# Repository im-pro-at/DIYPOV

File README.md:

# DIYPOV
 One POV Display to rule them all!

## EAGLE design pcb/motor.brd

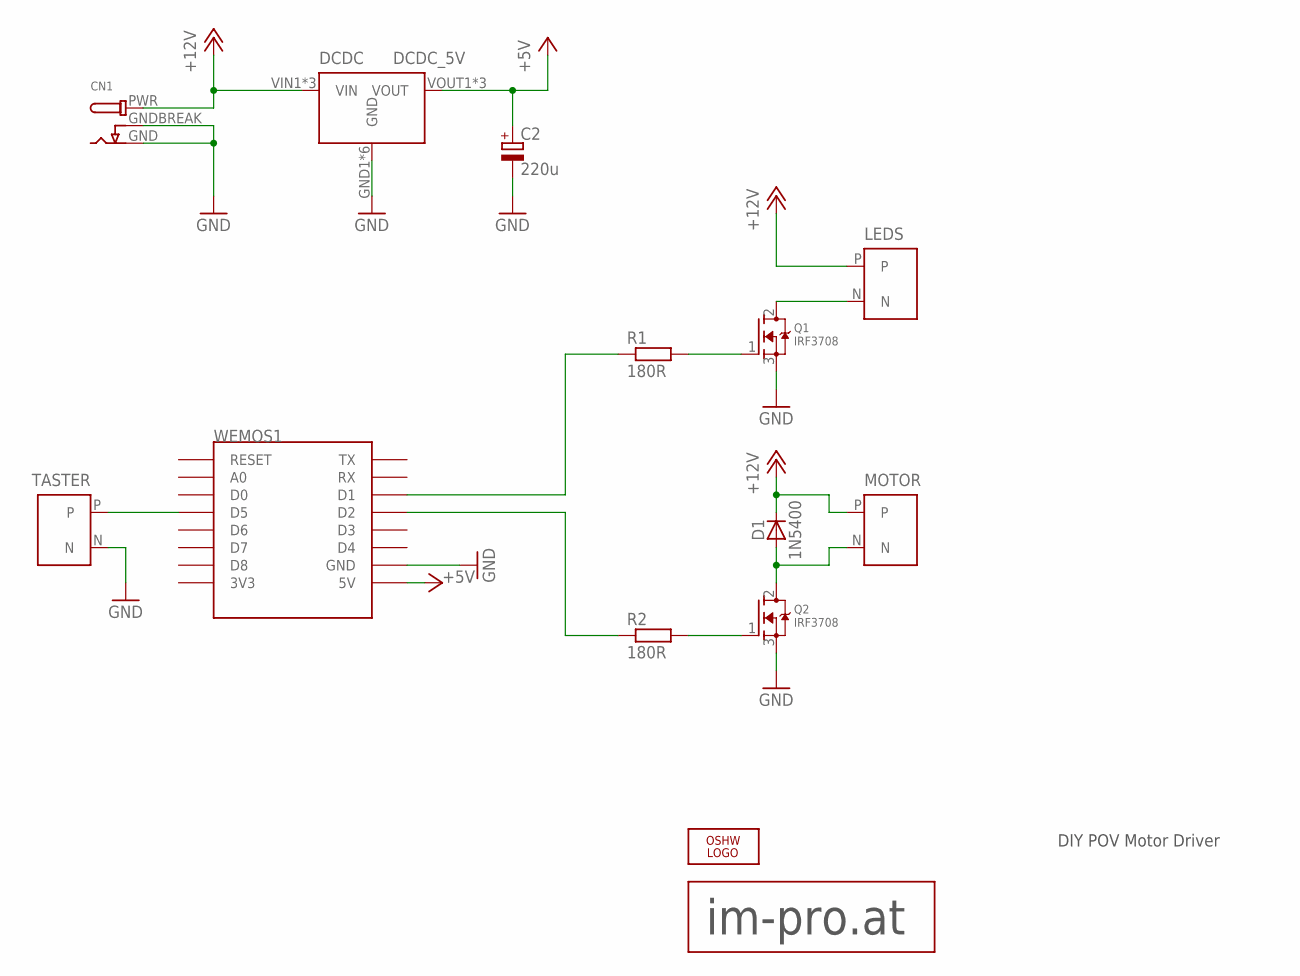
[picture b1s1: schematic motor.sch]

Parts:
C2: 220u; E3,5-8
CN1: DCBARRELPTH; DCJACK_2MM_PTH
D1: 1N5400; DO201-15
DCDC: DCDC_5V; DCDC
LEDS: TX30; XT30
LOGO1: OSHW_LOGO_FILLX0350-NT; OSHW_FILLX350_NOTEXT
MOTOR: TX30; XT30
Q1, Q2: IRF3708; TO220V
R1, R2: 180R; 0207/10
TASTER: TX30; XT30
U$1: LOGO20MM; LOGO_20MM
WEMOS1: WEMOS-D1-MINI

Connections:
+5V: C2.+, DCDC.VOUT1 (VOUT), DCDC.VOUT2 (VOUT), DCDC.VOUT3 (VOUT), WEMOS1.5V
+12V: CN1.PWR, D1.C, DCDC.VIN1 (VIN), DCDC.VIN2 (VIN), DCDC.VIN3 (VIN), LEDS.P, MOTOR.P
GND: C2.-, CN1.GND, CN1.GNDBREAK, DCDC.GND1 (GND), DCDC.GND2 (GND), DCDC.GND3 (GND), DCDC.GND4 (GND), DCDC.GND5 (GND), DCDC.GND6 (GND), Q1.3 (S), Q2.3 (S), TASTER.N, WEMOS1.GND
unnamed: D1.A, MOTOR.N, Q2.2 (D)
unnamed: LEDS.N, Q1.2 (D)
unnamed: R1.1, WEMOS1.D1
unnamed: TASTER.P, WEMOS1.D5
unnamed: R2.1, WEMOS1.D2
unnamed: Q2.1 (G), R2.2
unnamed: Q1.1 (G), R1.2

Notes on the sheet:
DIY POV Motor Driver

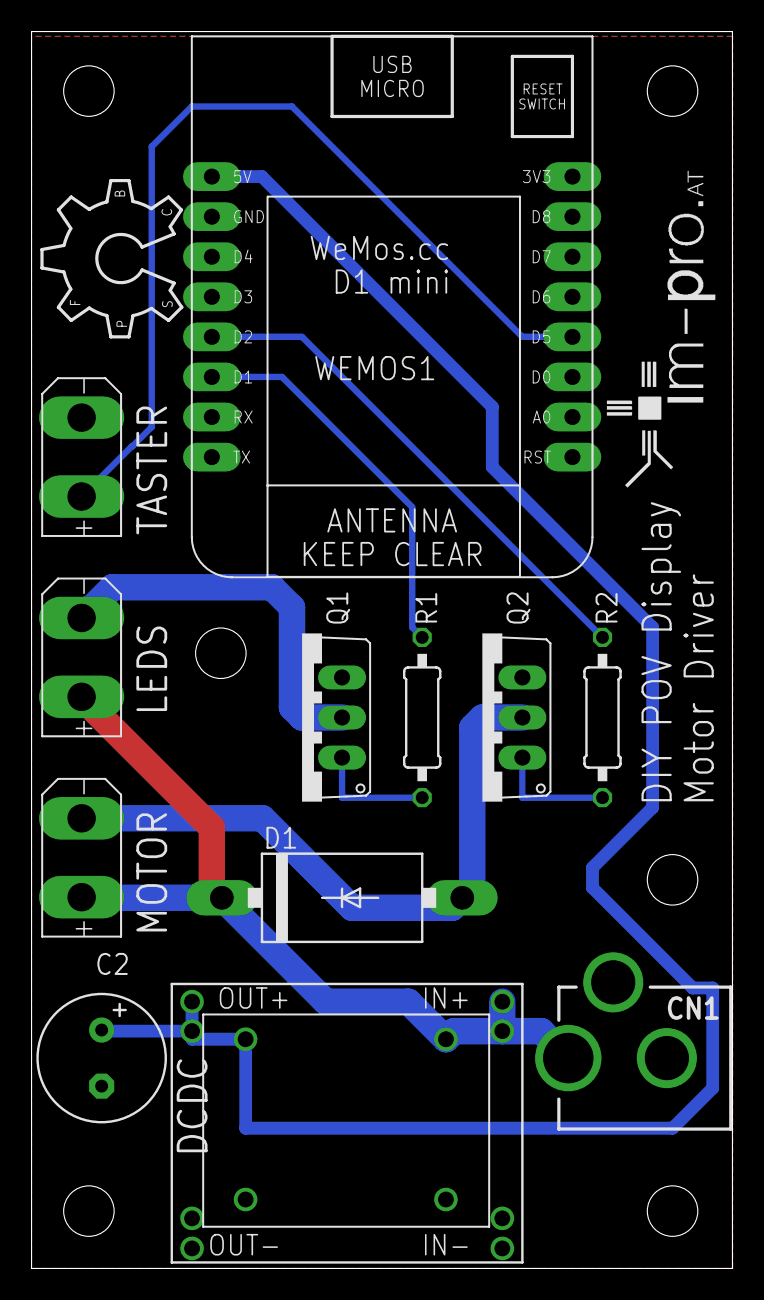
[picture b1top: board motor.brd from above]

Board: 2 copper layers, 44.4 x 78.4 mm, 14 parts (0 on the bottom side), 10 nets.

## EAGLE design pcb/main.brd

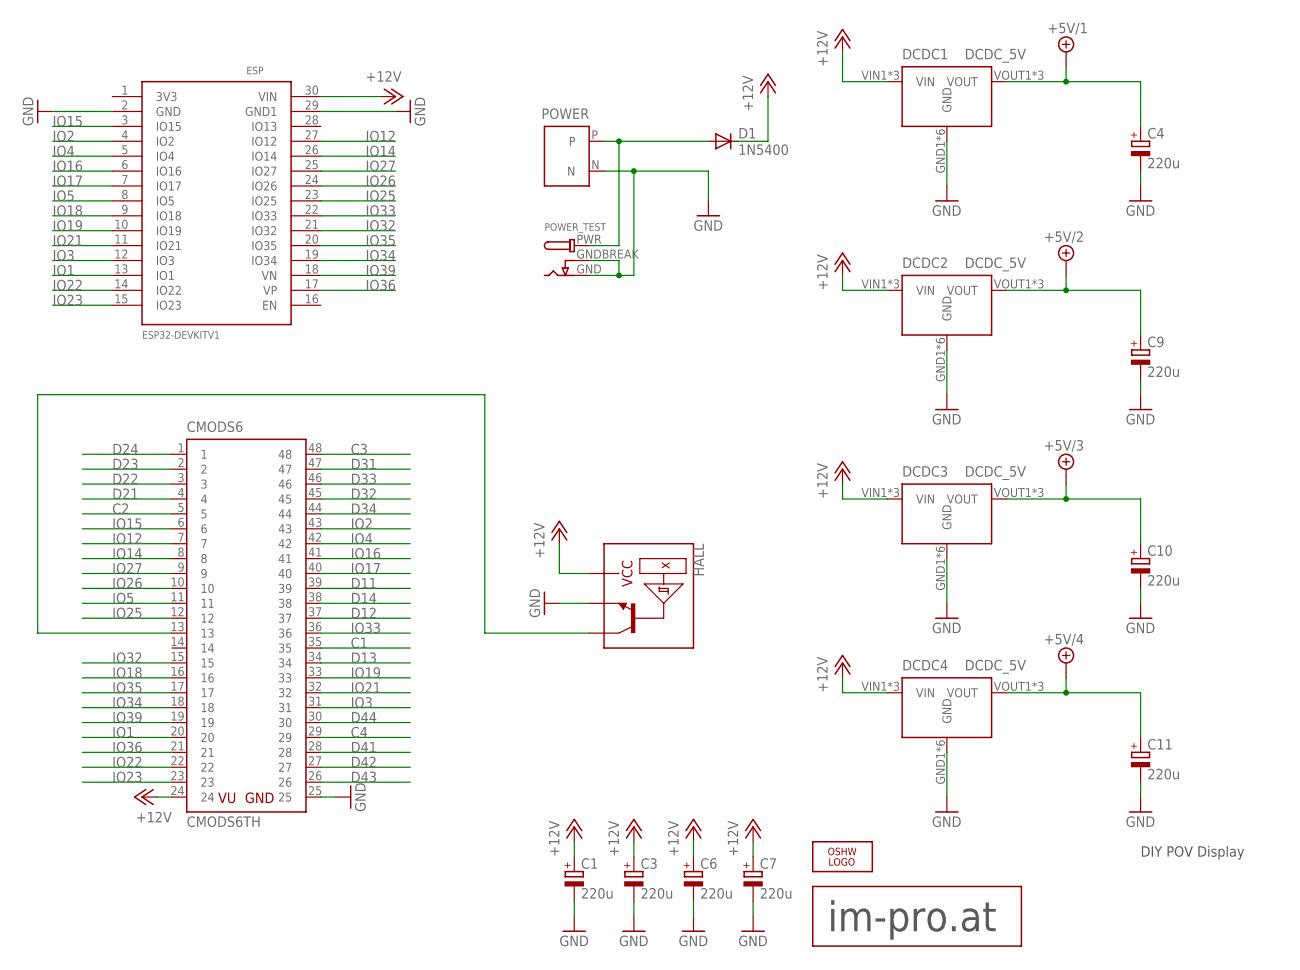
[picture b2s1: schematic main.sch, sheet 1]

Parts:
C1, C3, C4, C6, C7, C9, C10, C11: 220u; E3,5-8
CMODS6: CMODS6TH; DIL48
D1: 1N5400; DO201-15
DCDC1, DCDC2, DCDC3, DCDC4: DCDC_5V; DCDC
ESP: ESP32DEVKITV1; ESP32-DEVKITV1
HALL: HALL
LOGO1: OSHW_LOGO_FILLX0350-NT; OSHW_FILLX350_NOTEXT
POWER: TX30; XT30
POWER_TEST: DCBARRELPTH; DCJACK_2MM_PTH
U$2: LOGO20MM; LOGO_20MM

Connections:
+5V/1: C4.+, DCDC1.VOUT1 (VOUT), DCDC1.VOUT2 (VOUT), DCDC1.VOUT3 (VOUT); also elsewhere on the board
+5V/2: C9.+, DCDC2.VOUT1 (VOUT), DCDC2.VOUT2 (VOUT), DCDC2.VOUT3 (VOUT); also elsewhere on the board
+5V/3: C10.+, DCDC3.VOUT1 (VOUT), DCDC3.VOUT2 (VOUT), DCDC3.VOUT3 (VOUT); also elsewhere on the board
+5V/4: C11.+, DCDC4.VOUT1 (VOUT), DCDC4.VOUT2 (VOUT), DCDC4.VOUT3 (VOUT); also elsewhere on the board
+12V: C1.+, C3.+, C6.+, C7.+, CMODS6.24, D1.C, DCDC1.VIN1 (VIN), DCDC1.VIN2 (VIN), DCDC1.VIN3 (VIN), DCDC2.VIN1 (VIN), DCDC2.VIN2 (VIN), DCDC2.VIN3 (VIN), DCDC3.VIN1 (VIN), DCDC3.VIN2 (VIN), DCDC3.VIN3 (VIN), DCDC4.VIN1 (VIN), DCDC4.VIN2 (VIN), DCDC4.VIN3 (VIN), ESP.30 (VIN), HALL.VCC
C1: CMODS6.35; also elsewhere on the board
C2: CMODS6.5; also elsewhere on the board
C3: CMODS6.48; also elsewhere on the board
C4: CMODS6.29; also elsewhere on the board
D11: CMODS6.39; also elsewhere on the board
D12: CMODS6.37; also elsewhere on the board
D13: CMODS6.34; also elsewhere on the board
D14: CMODS6.38; also elsewhere on the board
D21: CMODS6.4; also elsewhere on the board
D22: CMODS6.3; also elsewhere on the board
D23: CMODS6.2; also elsewhere on the board
D24: CMODS6.1; also elsewhere on the board
D31: CMODS6.47; also elsewhere on the board
D32: CMODS6.45; also elsewhere on the board
D33: CMODS6.46; also elsewhere on the board
D34: CMODS6.44; also elsewhere on the board
D41: CMODS6.28; also elsewhere on the board
D42: CMODS6.27; also elsewhere on the board
D43: CMODS6.26; also elsewhere on the board
D44: CMODS6.30; also elsewhere on the board
GND: C1.-, C3.-, C4.-, C6.-, C7.-, C9.-, C10.-, C11.-, CMODS6.25, DCDC1.GND1 (GND), DCDC1.GND2 (GND), DCDC1.GND3 (GND), DCDC1.GND4 (GND), DCDC1.GND5 (GND), DCDC1.GND6 (GND), DCDC2.GND1 (GND), DCDC2.GND2 (GND), DCDC2.GND3 (GND), DCDC2.GND4 (GND), DCDC2.GND5 (GND), DCDC2.GND6 (GND), DCDC3.GND1 (GND), DCDC3.GND2 (GND), DCDC3.GND3 (GND), DCDC3.GND4 (GND), DCDC3.GND5 (GND), DCDC3.GND6 (GND), DCDC4.GND1 (GND), DCDC4.GND2 (GND), DCDC4.GND3 (GND), DCDC4.GND4 (GND), DCDC4.GND5 (GND), DCDC4.GND6 (GND), ESP.2 (GND), ESP.29 (GND1), HALL.GND, POWER.N, POWER_TEST.GND, POWER_TEST.GNDBREAK; also elsewhere on the board
IO1: CMODS6.20, ESP.13 (IO1)
IO2: CMODS6.43, ESP.4 (IO2)
IO3: CMODS6.31, ESP.12 (IO3)
IO4: CMODS6.42, ESP.5 (IO4)
IO5: CMODS6.11, ESP.8 (IO5)
IO12: CMODS6.7, ESP.27 (IO12)
IO14: CMODS6.8, ESP.26 (IO14)
IO15: CMODS6.6, ESP.3 (IO15)
IO16: CMODS6.41, ESP.6 (IO16)
IO17: CMODS6.40, ESP.7 (IO17)
IO18: CMODS6.16, ESP.9 (IO18)
IO19: CMODS6.33, ESP.10 (IO19)
IO21: CMODS6.32, ESP.11 (IO21)
IO22: CMODS6.22, ESP.14 (IO22)
IO23: CMODS6.23, ESP.15 (IO23)
IO25: CMODS6.12, ESP.23 (IO25)
IO26: CMODS6.10, ESP.24 (IO26)
IO27: CMODS6.9, ESP.25 (IO27)
IO32: CMODS6.15, ESP.21 (IO32)
IO33: CMODS6.36, ESP.22 (IO33)
IO34: CMODS6.18, ESP.19 (IO34)
IO35: CMODS6.17, ESP.20 (IO35)
IO36: CMODS6.21, ESP.17 (VP)
IO39: CMODS6.19, ESP.18 (VN)
unnamed: CMODS6.13, HALL.OUT
unnamed: D1.A, POWER.P, POWER_TEST.PWR

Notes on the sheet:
DIY POV Display

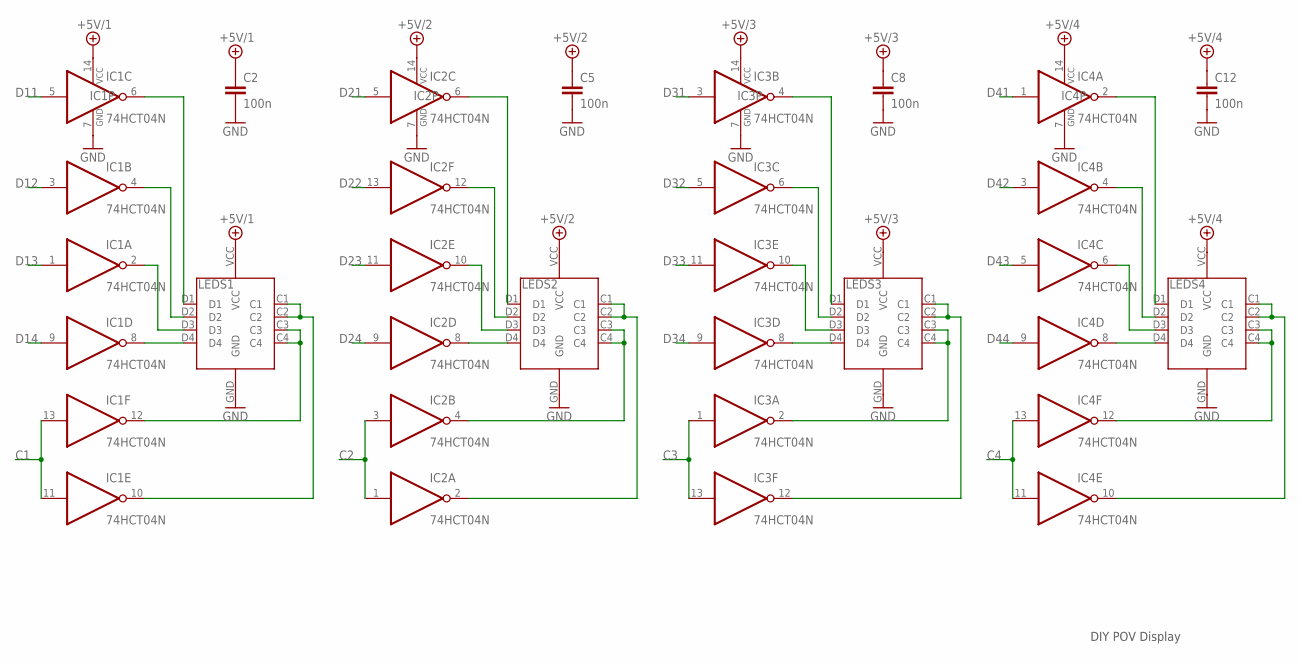
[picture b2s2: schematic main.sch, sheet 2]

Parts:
C2, C5, C8, C12: 100n; C025_050-025X075
IC1, IC2, IC3, IC4: 74HCT04N; DIL14
LEDS1, LEDS2, LEDS3, LEDS4: LEDCON

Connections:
+5V/1: C2.1, IC1.14 (VCC), LEDS1.VCC; also elsewhere on the board
+5V/2: C5.1, IC2.14 (VCC), LEDS2.VCC; also elsewhere on the board
+5V/3: C8.1, IC3.14 (VCC), LEDS3.VCC; also elsewhere on the board
+5V/4: C12.1, IC4.14 (VCC), LEDS4.VCC; also elsewhere on the board
C1: IC1.11 (I), IC1.13 (I); also elsewhere on the board
C2: IC2.1 (I), IC2.3 (I); also elsewhere on the board
C3: IC3.1 (I), IC3.13 (I); also elsewhere on the board
C4: IC4.11 (I), IC4.13 (I); also elsewhere on the board
D11: IC1.5 (I); also elsewhere on the board
D12: IC1.3 (I); also elsewhere on the board
D13: IC1.1 (I); also elsewhere on the board
D14: IC1.9 (I); also elsewhere on the board
D21: IC2.5 (I); also elsewhere on the board
D22: IC2.13 (I); also elsewhere on the board
D23: IC2.11 (I); also elsewhere on the board
D24: IC2.9 (I); also elsewhere on the board
D31: IC3.3 (I); also elsewhere on the board
D32: IC3.5 (I); also elsewhere on the board
D33: IC3.11 (I); also elsewhere on the board
D34: IC3.9 (I); also elsewhere on the board
D41: IC4.1 (I); also elsewhere on the board
D42: IC4.3 (I); also elsewhere on the board
D43: IC4.5 (I); also elsewhere on the board
D44: IC4.9 (I); also elsewhere on the board
GND: C2.2, C2.3 (2), C5.2, C5.3 (2), C8.2, C8.3 (2), C12.2, C12.3 (2), IC1.7 (GND), IC2.7 (GND), IC3.7 (GND), IC4.7 (GND), LEDS1.GND, LEDS2.GND, LEDS3.GND, LEDS4.GND; also elsewhere on the board
unnamed: IC1.8 (O), LEDS1.D4
unnamed: IC1.2 (O), LEDS1.D3
unnamed: IC1.4 (O), LEDS1.D2
unnamed: IC1.6 (O), LEDS1.D1
unnamed: IC1.12 (O), LEDS1.C3, LEDS1.C4
unnamed: IC1.10 (O), LEDS1.C1, LEDS1.C2
unnamed: IC2.8 (O), LEDS2.D4
unnamed: IC2.10 (O), LEDS2.D3
unnamed: IC2.12 (O), LEDS2.D2
unnamed: IC2.6 (O), LEDS2.D1
unnamed: IC2.4 (O), LEDS2.C3, LEDS2.C4
unnamed: IC2.2 (O), LEDS2.C1, LEDS2.C2
unnamed: IC3.8 (O), LEDS3.D4
unnamed: IC3.10 (O), LEDS3.D3
unnamed: IC3.6 (O), LEDS3.D2
unnamed: IC3.4 (O), LEDS3.D1
unnamed: IC3.2 (O), LEDS3.C3, LEDS3.C4
unnamed: IC3.12 (O), LEDS3.C1, LEDS3.C2
unnamed: IC4.8 (O), LEDS4.D4
unnamed: IC4.6 (O), LEDS4.D3
unnamed: IC4.4 (O), LEDS4.D2
unnamed: IC4.2 (O), LEDS4.D1
unnamed: IC4.12 (O), LEDS4.C3, LEDS4.C4
unnamed: IC4.10 (O), LEDS4.C1, LEDS4.C2

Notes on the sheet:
DIY POV Display

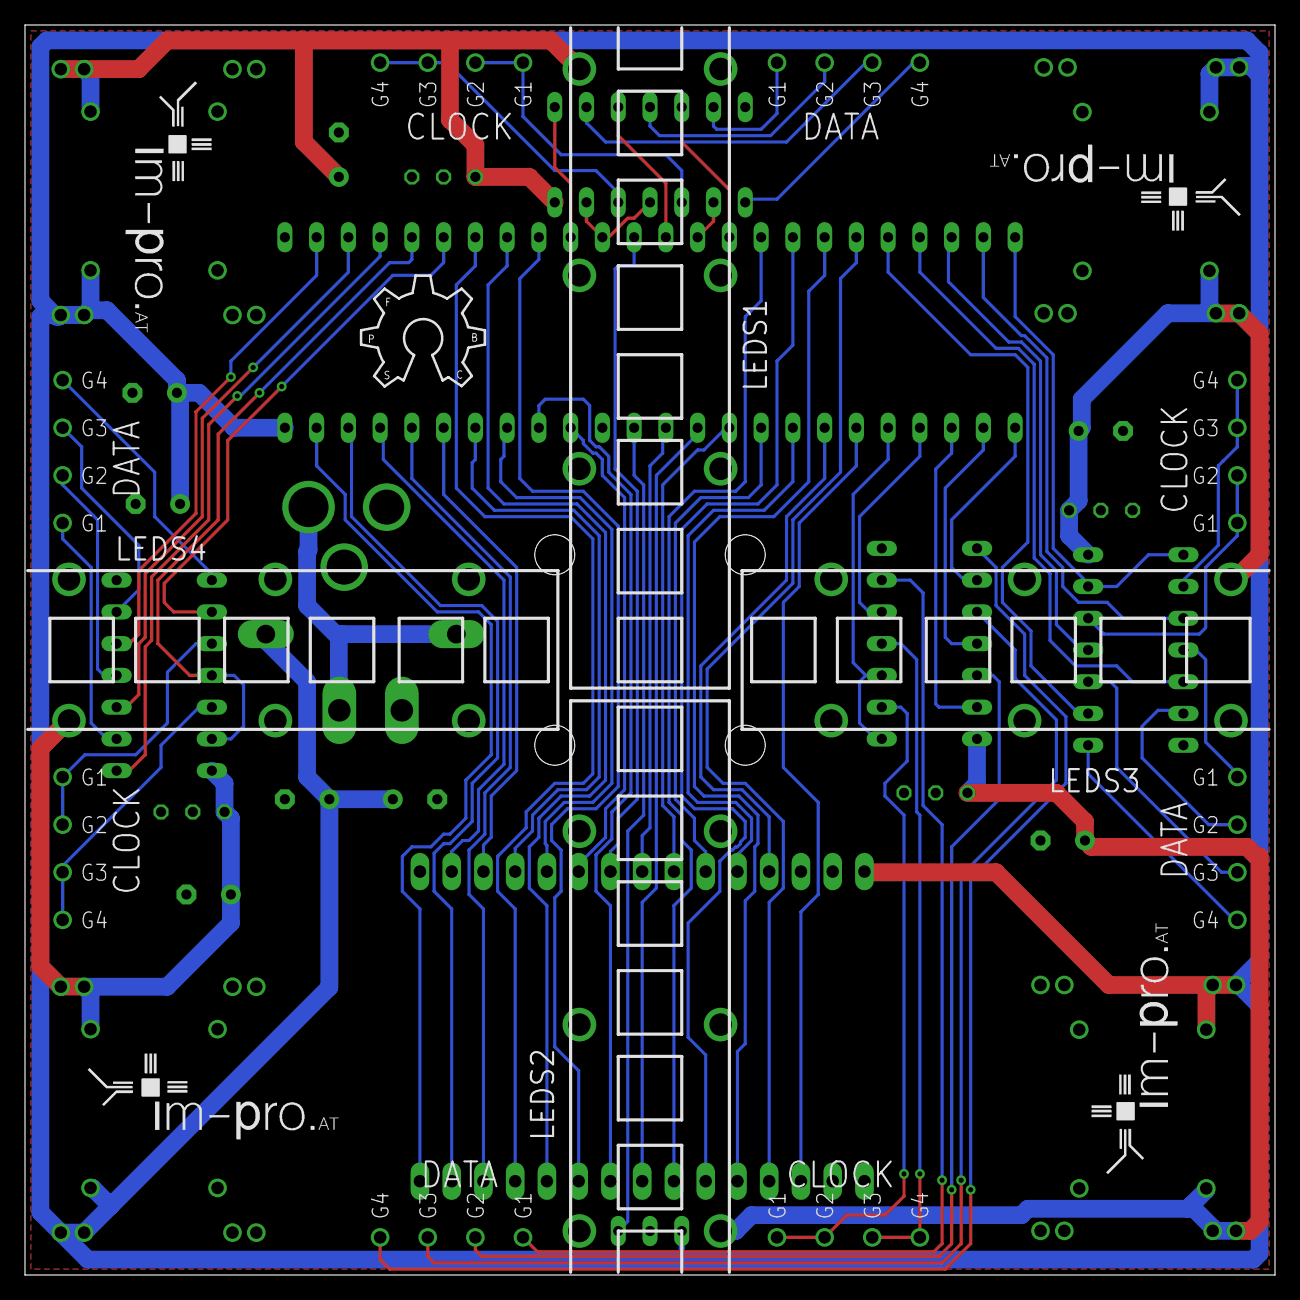
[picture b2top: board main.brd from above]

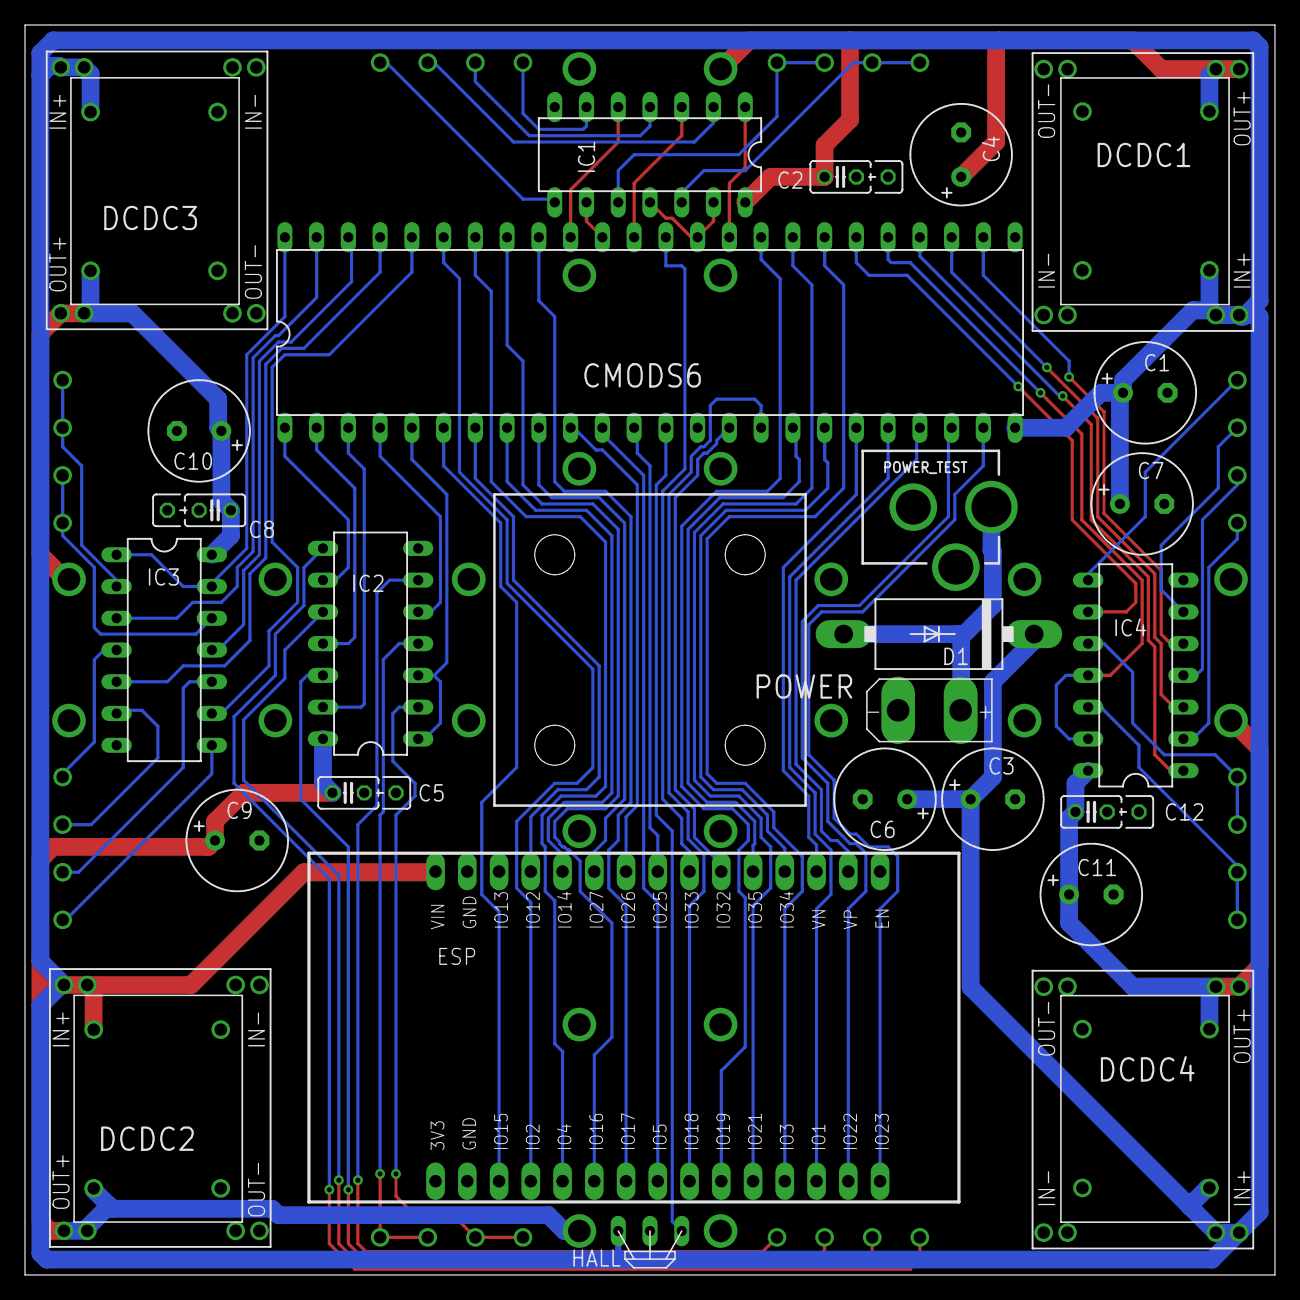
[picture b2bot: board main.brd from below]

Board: 2 copper layers, 100.0 x 100.0 mm, 35 parts (26 on the bottom side), 76 nets.

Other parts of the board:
U$1, U$3, U$4: LOGO20MM; LOGO_20MM

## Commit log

2019-08-28 Initial commit: Copied data from POV project
2019-08-28 Add first changes to the 3D design
2019-08-31 updated schematic for main board
2019-09-01 updated schematic for motor driver
2019-09-05 first version of motor driver pcb layout
2019-09-06 started layout of main pcb
2019-09-07 first version layout main pcb
2019-09-07 finished main pcb layout
2019-09-08 layout finished
2019-09-11 started to implement arduino code for the ESP32
2019-09-19 3D design update
2019-09-21 finished 3D model
2019-09-25 First useful version of ESP32 Firmware
2019-09-29 first functional release

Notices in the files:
parts and their libraries:
microbuilder: This work is placed in the public domain, and may be freely used for commercial and non-commercial work with the following conditions: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
